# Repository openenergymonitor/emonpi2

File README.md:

# emonPi v2

The emonPi2 is an energy monitor that can monitor up to 6 AC circuits using CT sensors and the OpenEnergyMonitor emonVs voltage sensing unit. It consists of a measurement board that sits on top of a RaspberryPi. The measurement board features the Microchip AVR128DB348 microcontroller - responsible for sampling the current and voltage waveforms and calculating the power and energy values. The RaspberryPi provides full local data logging and visualisation capability. The emonPi2 can also be used as a basestation to receive data from other 433Mhz radio nodes.

**Features**

- 6 CT sensor inputs (333mV voltage output CT's)
- RJ45: 1-3 phase voltage input
- Pulse and temperature sensing input
- Micro: AVR128DB48
- MCP1501 Precision reference
- RFM69CW radio
- USB-C
- I2C 128x64 SSD1306 Display
- RTC I2C Breakout
- Optional on-board UART

### [Hardware schematic and board files](hardware)

### [Firmware](firmware)

### Community & Support

- [OpenEnergyMonitor Forums](https://community.openenergymonitor.org)

OpenEnergyMonitor Shop Support: support@openenergymonitor.zendesk.com

### License

- The hardware designs (schematics and CAD files) are licensed under a Creative Commons Attribution-ShareAlike 3.0 Unported License.
- The firmware is released under the GNU GPL V3 license The documentation is subject to GNU Free Documentation License
- The hardware designs follow the terms of the OSHW (Open-source hardware) Statement of Principles 1.0.

### Disclaimer

```
OUR PRODUCTS AND ASSEMBLY KITS MAY BE USED BY EXPERIENCED, SKILLED USERS, AT THEIR OWN RISK. TO THE FULLEST EXTENT PERMISSIBLE BY THE APPLICABLE LAW, WE HEREBY DISCLAIM ANY AND ALL RESPONSIBILITY, RISK, LIABILITY AND DAMAGES ARISING OUT OF DEATH OR PERSONAL INJURY RESULTING FROM ASSEMBLY OR OPERATION OF OUR PRODUCTS.

Your safety is your own responsibility, including proper use of equipment and safety gear, and determining whether you have adequate skill and experience. OpenEnergyMonitor and Megni registered partnership disclaims all responsibility for any resulting damage, injury, or expense. It is your responsibility to make sure that your activities comply with applicable laws, including copyright. Always check the webpage associated with each unit before you get started. There may be important updates or corrections. All use of the instructions, kits, projects and suggestions given both by megni.co.uk, openenergymonitor.org and shop.openenergymonitor.org are to be used at your own risk. The technology (hardware , firmware and software) are constantly changing, documentation (including build guide and instructions) may not be complete or correct.

If you feel uncomfortable with assembling or using any part of the system, return it to us for a full refund.
```

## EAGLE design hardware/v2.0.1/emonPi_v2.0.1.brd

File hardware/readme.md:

# emonPi2 - Hardware

## Change Log 

### V2.0.0

First release 

### V2.0.1

**manufactured in April 2023**

- DFM tweaks 
- Fix pad sizes 
- Change USB-C connector footprint and enable duel orientation data connections 

The emonPi2 hardware schematics and board files have been developed using Eagle (now Autodesk). A free version is available to download here: https://www.autodesk.co.uk/products/eagle/free-download.

Alternatively it is also possible to open these board designs using KiKad which is open source.

**Schematic:**

**Board design:**

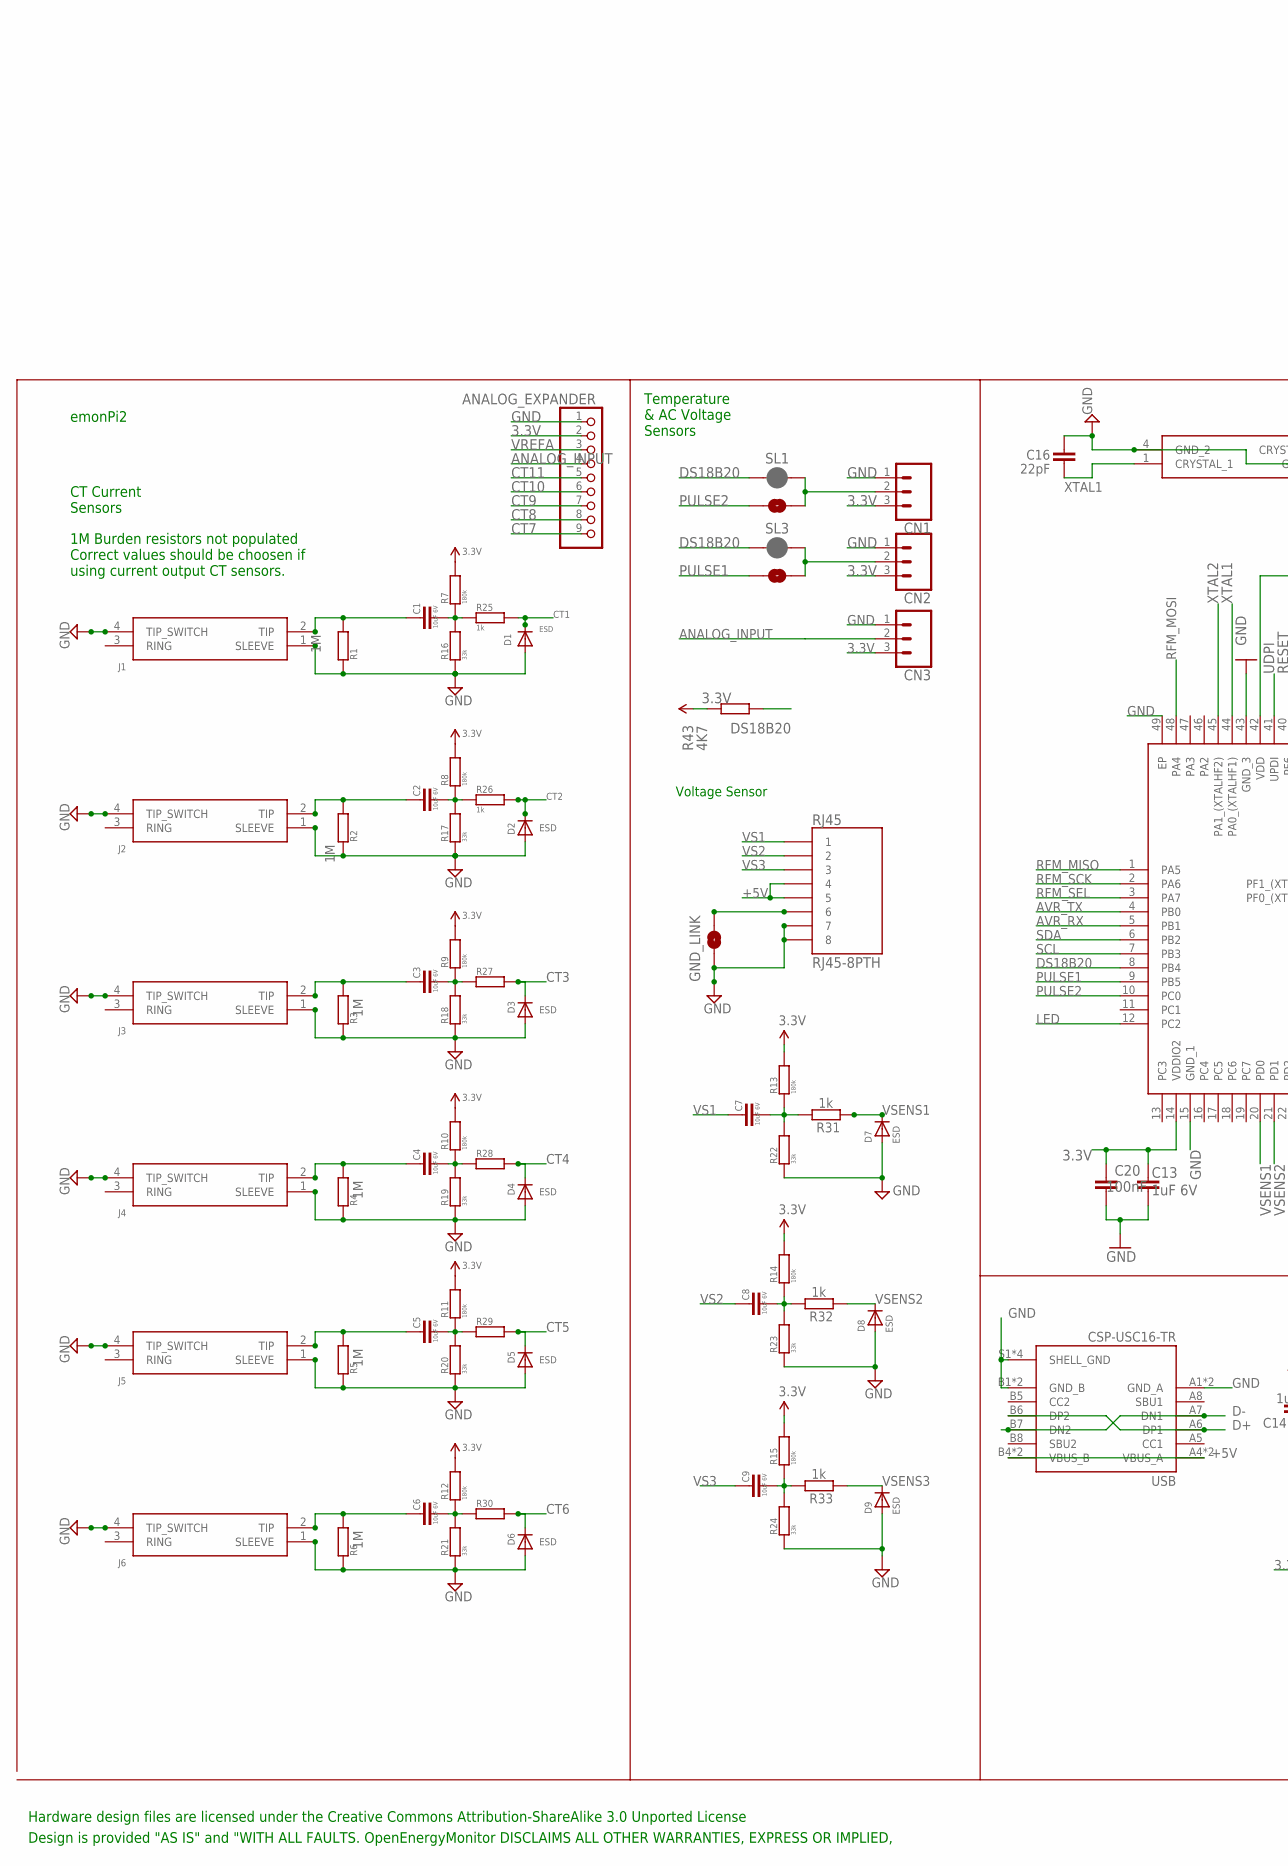
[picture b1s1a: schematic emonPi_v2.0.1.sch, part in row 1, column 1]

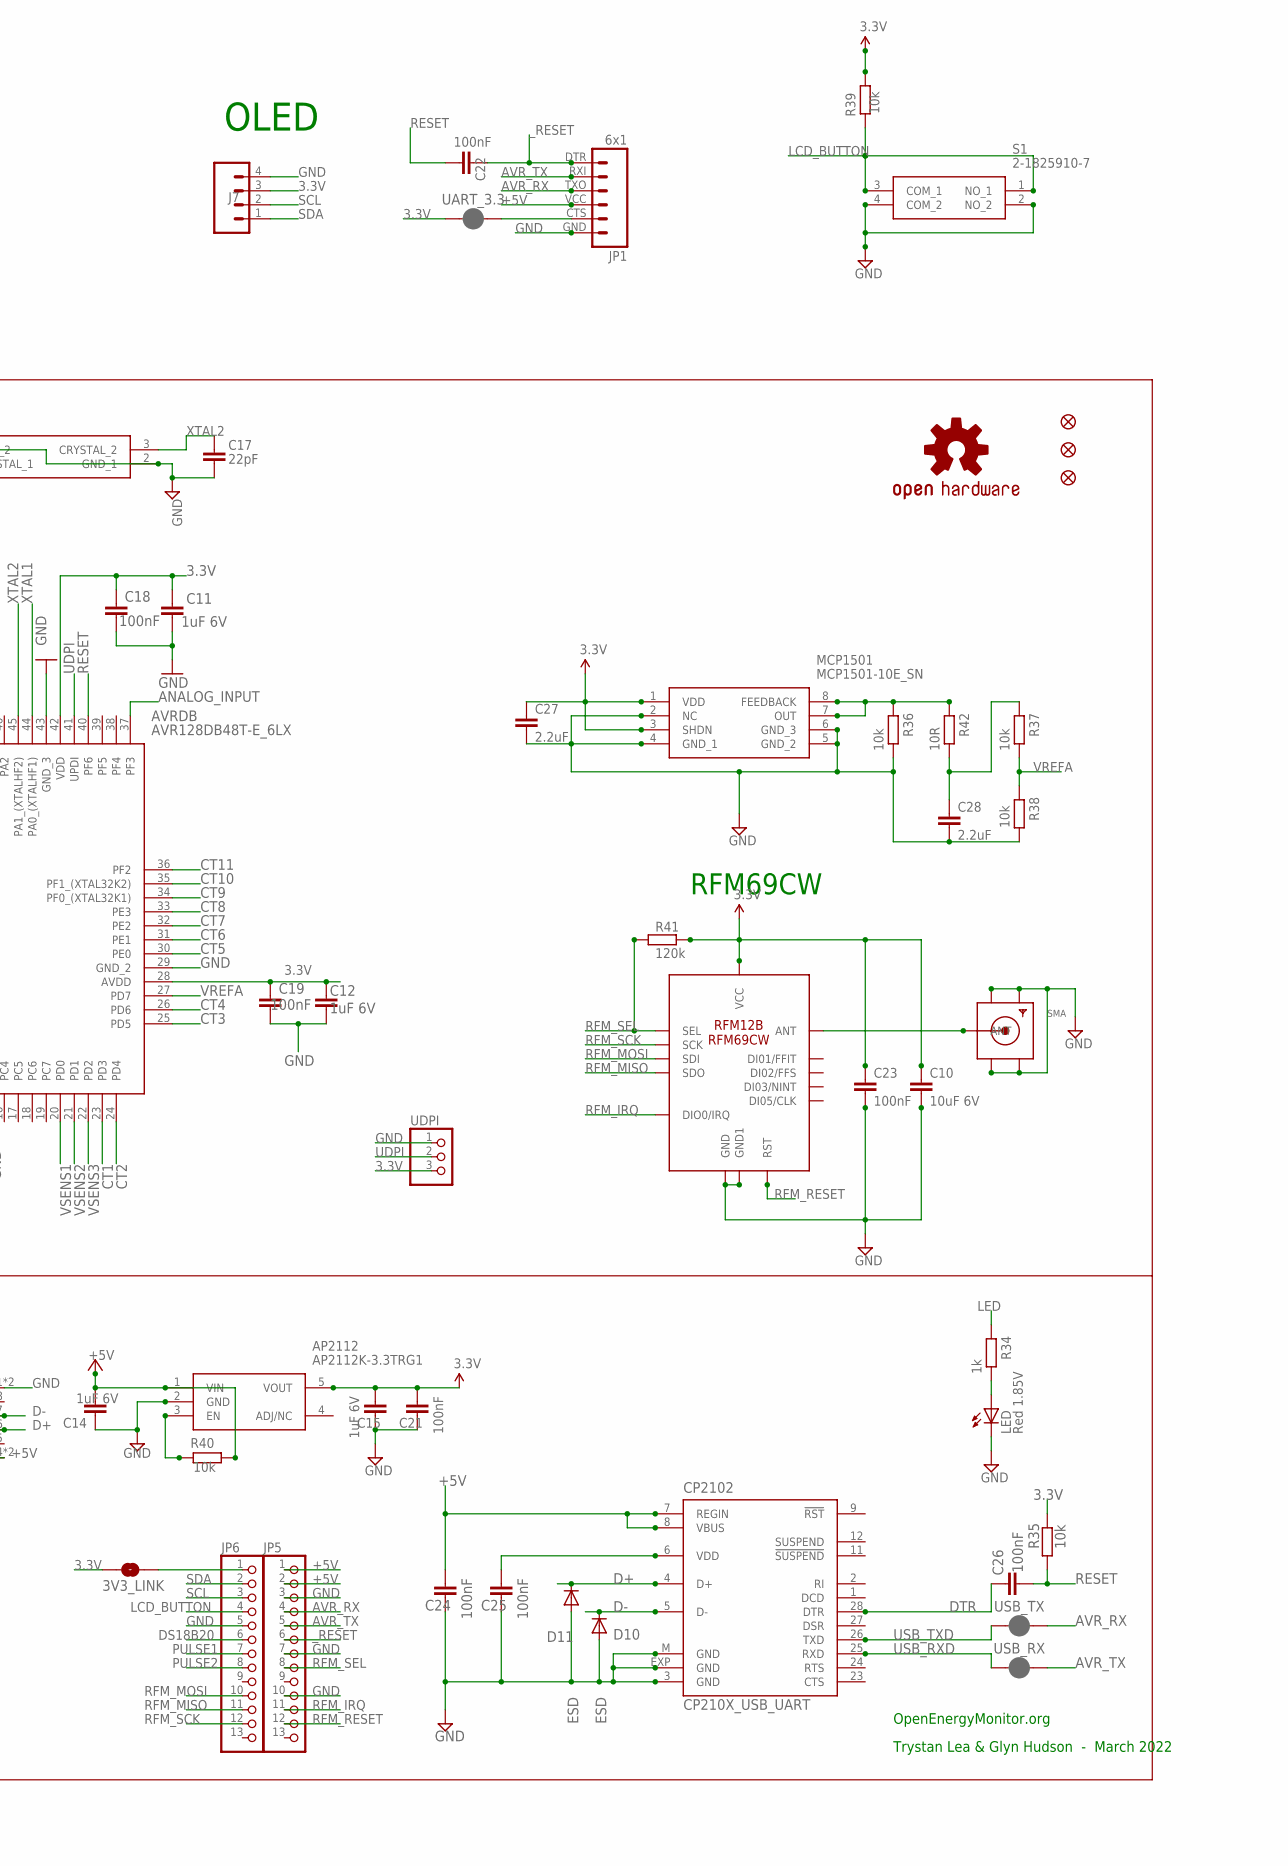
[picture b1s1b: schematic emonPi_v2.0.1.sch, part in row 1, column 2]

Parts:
3V3_LINK: SOLDERJUMPERNC; SJ_2S
ANALOG_EXPANDER: PINHD-1X9; 1X09-BIG
AP2112: AP2112K-3.3TRG1; SOT95P282X130-5N
AVRDB: AVR128DB48T-E_6LX; QFN40P600X600X90-49N
C1, C2, C3, C4, C5, C6, C7, C8, C9, C10: 10uF 6V; C0603
C11, C12, C13, C14, C15: 1uF 6V; C0603
C16, C17: 22pF; C0603
C18, C19, C20, C21, C22, C23, C24, C25, C26: 100nF; C0603
C27, C28: 2.2uF; C0603
CN1, CN2, CN3: CONN_03SCREW; SCREWTERMINAL-3.5MM-3
CP2102: CP210X_USB_UART; MLP28
D1, D2, D3, D4, D5, D6, D7, D8, D9, D10, D11: ESD; SOD-523
FD1, FD2, FD3: FIDUCIAL1X2; FIDUCIAL-1X2
GND_LINK: SOLDERJUMPERNC; SJ_2S
J1, J2, J3, J4, J5, J6: SJ-3524-SMT-TR
J7: CONN_04PTH; 1X04
JP1: 6x1; FTDI_BASIC
JP5, JP6: PINHD-1X13_BIG; 1X13-BIG
LED: Red 1.85V; CHIP-LED0805
LOGO1: OSHW-LOGOS-COPPER; OSHW-LOGO-S_COPPER
MCP1501: MCP1501-10E_SN; SOIC127P600X175-8N
R1, R2, R3, R4, R5, R6: 1M; R1206
R7, R8, R9, R10, R11, R12, R13, R14, R15: 180k; R0603
R16, R17, R18, R19, R20, R21, R22, R23, R24: 33k; R0603
R25, R26, R27, R28, R29, R30, R31, R32, R33, R34: 1k; R0603
R35, R36, R37, R38, R39, R40: 10k; R0603
R41: 120k; R0603
R42: 10R; R0603
R43: 4K7; R0603
RFM69: RFM12B/69CW
RJ45: RJ45-8PTH; RJ45-8
S1: 2-1825910-7; 218259107
SL1, SL3: JUMPER-SMT_2_NC_PASTE_NO-SILK; SMT-JUMPER_2_NC_PASTE_NO-SILK
SL2, SL4: SOLDERJUMPERNC; SJ_2S
SMA: SMACONNECTOR; SMA90_DIP
UART_3.3: JUMPER-SMT_2_NC_PASTE_NO-SILK; SMT-JUMPER_2_NC_PASTE_NO-SILK
UDPI: PINHD-1X3; 1X03
USB: CSP-USC16-TR; VALCON_CSP-USC16-TR
USB_RX: JUMPER-SMT_2_NC_PASTE_NO-SILK; SMT-JUMPER_2_NC_PASTE_NO-SILK
USB_TX: JUMPER-SMT_2_NC_PASTE_NO-SILK; SMT-JUMPER_2_NC_PASTE_NO-SILK
XTAL: MCSJK-7U-12.00-12-10-80-B-10; MCSJK7U1200121080B10

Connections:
3.3V: 3V3_LINK.1, ANALOG_EXPANDER.2, AP2112.5 (VOUT), AVRDB.14 (VDDIO2), AVRDB.28 (AVDD), AVRDB.42 (VDD), C10.1, C11.1, C12.1, C13.1, C15.2, C18.1, C19.1, C20.1, C21.2, C23.1, C27.1, CN1.3, CN2.3, CN3.3, J7.3, MCP1501.1 (VDD), MCP1501.3 (SHDN), R7.2, R8.2, R9.2, R10.2, R11.2, R12.2, R13.2, R14.2, R15.2, R35.2, R39.1, R41.2, R43.1, RFM69.VDD (VCC), UART_3.3.1, UDPI.3
+5V: AP2112.1 (VIN), C14.2, C24.2, CP2102.7 (REGIN), CP2102.8 (VBUS), JP1.VCC (4), JP5.1, JP5.2, R40.1, RJ45.4, RJ45.5, USB.A4 (VBUS_A), USB.A9 (VBUS_A), USB.B4 (VBUS_B), USB.B9 (VBUS_B)
ANALOG_INPUT: ANALOG_EXPANDER.4, AVRDB.37 (PF3), CN3.2
AVR_RX: AVRDB.5 (PB1), JP1.TXO (3), JP5.4, USB_TX.2
AVR_TX: AVRDB.4 (PB0), JP1.RXI (2), JP5.5, USB_RX.2
CT1: AVRDB.23 (PD3), D1.K (C), R25.2
CT2: AVRDB.24 (PD4), D2.K (C), R26.2
CT3: AVRDB.25 (PD5), D3.K (C), R27.1
CT4: AVRDB.26 (PD6), D4.K (C), R28.1
CT5: AVRDB.30 (PE0), D5.K (C), R29.1
CT6: AVRDB.31 (PE1), D6.K (C), R30.1
CT7: ANALOG_EXPANDER.9, AVRDB.32 (PE2)
CT8: ANALOG_EXPANDER.8, AVRDB.33 (PE3)
CT9: ANALOG_EXPANDER.7, AVRDB.34 (PF0_(XTAL32K1))
CT10: ANALOG_EXPANDER.6, AVRDB.35 (PF1_(XTAL32K2))
CT11: ANALOG_EXPANDER.5, AVRDB.36 (PF2)
D+: CP2102.4 (D+), D11.K (C), USB.A6 (DP1), USB.B6 (DP2)
D-: CP2102.5 (D-), D10.K (C), USB.A7 (DN1), USB.B7 (DN2)
DIG1: RFM69.ANT, SMA.ANTENNA (ANT)
DS18B20: AVRDB.8 (PB4), JP6.6, R43.2, SL1.1, SL3.1
DTR: C26.1, CP2102.28 (DTR)
GND: ANALOG_EXPANDER.1, AP2112.2 (GND), AVRDB.15 (GND_1), AVRDB.29 (GND_2), AVRDB.43 (GND_3), AVRDB.49 (EP), C10.2, C11.2, C12.2, C13.2, C14.1, C15.1, C16.1, C17.2, C18.2, C19.2, C20.2, C21.1, C23.2, C24.1, C25.1, C27.2, C28.2, CN1.1, CN2.1, CN3.1, CP2102.3 (GND), CP2102.EXP (GND), CP2102.M (GND), D1.A, D2.A, D3.A, D4.A, D5.A, D6.A, D7.A, D8.A, D9.A, D10.A, D11.A, GND_LINK.1, J1.1 (SLEEVE), J1.4 (TIP_SWITCH), J2.1 (SLEEVE), J2.4 (TIP_SWITCH), J3.1 (SLEEVE), J3.4 (TIP_SWITCH), J4.1 (SLEEVE), J4.4 (TIP_SWITCH), J5.1 (SLEEVE), J5.4 (TIP_SWITCH), J6.1 (SLEEVE), J6.4 (TIP_SWITCH), J7.4, JP1.GND (6), JP5.3, JP5.7, JP5.10, JP6.5, LED.C, MCP1501.2 (NC), MCP1501.4 (GND_1), MCP1501.5 (GND_2), MCP1501.6 (GND_3), R1.1, R2.1, R3.1, R4.1, R5.1, R6.1, R16.2, R17.2, R18.2, R19.2, R20.2, R21.2, R22.2, R23.1, R24.1, R36.1, R38.1, RFM69.GND, RFM69.GND1, RJ45.7, RJ45.8, S1.2 (NO_2), S1.4 (COM_2), SMA.GND1, SMA.GND2, SMA.GND3, SMA.GND4, UDPI.1, USB.A1 (GND_A), USB.A12 (GND_A), USB.B1 (GND_B), USB.B12 (GND_B), USB.S1 (SHELL_GND), USB.S2 (SHELL_GND), USB.S3 (SHELL_GND), USB.S4 (SHELL_GND), XTAL.2 (GND_1), XTAL.4 (GND_2)
LCD_BUTTON: JP6.4, R39.2, S1.1 (NO_1), S1.3 (COM_1)
LED: AVRDB.12 (PC2), R34.2
unnamed: C1.1, J1.2 (TIP), R1.2
unnamed: C7.2, R13.1, R22.1, R31.2
unnamed: C3.1, J3.2 (TIP), R3.2
unnamed: C8.2, R14.1, R23.2, R32.2
unnamed: C4.1, J4.2 (TIP), R4.2
unnamed: C9.2, R15.1, R24.2, R33.2
unnamed: C2.1, J2.2 (TIP), R2.2
unnamed: C5.1, J5.2 (TIP), R5.2
unnamed: C5.2, R11.1, R20.1, R29.2
unnamed: C2.2, R8.1, R17.1, R26.1
unnamed: C4.2, R10.1, R19.1, R28.2
unnamed: C1.2, R7.1, R16.1, R25.1
unnamed: C6.1, J6.2 (TIP), R6.2
unnamed: C6.2, R12.1, R21.1, R30.2
unnamed: C3.2, R9.1, R18.1, R27.2
unnamed: CN1.2, SL1.2, SL2.2
unnamed: CN2.2, SL3.2, SL4.2
unnamed: GND_LINK.2, RJ45.6
unnamed: AP2112.3 (EN), R40.2
unnamed: C28.1, R37.2, R42.1
unnamed: MCP1501.7 (OUT), MCP1501.8 (FEEDBACK), R36.2, R42.2
unnamed: 3V3_LINK.2, JP6.1
unnamed: C25.2, CP2102.6 (VDD)
unnamed: JP1.CTS (5), UART_3.3.2
unnamed: LED.A, R34.1
PULSE1: AVRDB.9 (PB5), JP6.7, SL4.1
PULSE2: AVRDB.10 (PC0), JP6.8, SL2.1
RESET: AVRDB.40 (PF6), C22.2, C26.2, R35.1
RFM_IRQ: JP5.11, RFM69.IRQ (DIO0/IRQ)
RFM_MISO: AVRDB.1 (PA5), JP6.11, RFM69.SDO
RFM_MOSI: AVRDB.48 (PA4), JP6.10, RFM69.SDI
RFM_RESET: JP5.12, RFM69.RST
RFM_SCK: AVRDB.2 (PA6), JP6.12, RFM69.SCK
RFM_SEL: AVRDB.3 (PA7), JP5.8, R41.1, RFM69.SEL
SCL: AVRDB.7 (PB3), J7.2, JP6.3
SDA: AVRDB.6 (PB2), J7.1, JP6.2
UDPI: AVRDB.41 (UPDI), UDPI.2
USB_RXD: CP2102.25 (RXD), USB_RX.1
USB_TXD: CP2102.26 (TXD), USB_TX.1
VREFA: ANALOG_EXPANDER.3, AVRDB.27 (PD7), R37.1, R38.2
VS1: C7.1, RJ45.1
VS2: C8.1, RJ45.2
VS3: C9.1, RJ45.3
VSENS1: AVRDB.20 (PD0), D7.K (C), R31.1
VSENS2: AVRDB.21 (PD1), D8.K (C), R32.1
VSENS3: AVRDB.22 (PD2), D9.K (C), R33.1
XTAL1: AVRDB.44 (PA0_(XTALHF1)), C16.2, XTAL.1 (CRYSTAL_1)
XTAL2: AVRDB.45 (PA1_(XTALHF2)), C17.1, XTAL.3 (CRYSTAL_2)
_RESET: C22.1, JP1.DTR (1), JP5.6

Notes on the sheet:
Voltage Sensor
RFM69CW
OLED
emonPi2
Temperature & AC Voltage Sensors
Design is provided "AS IS" and "WITH ALL FAULTS. OpenEnergyMonitor DISCLAIMS ALL OTHER WARRANTIES, EXPRESS OR IMPLIED,
Hardware design files are licensed under the Creative Commons Attribution-ShareAlike 3.0 Unported License
OpenEnergyMonitor.org
Trystan Lea & Glyn Hudson - March 2022
1M Burden resistors not populated Correct values should be choosen if using current output CT sensors.
CT Current Sensors

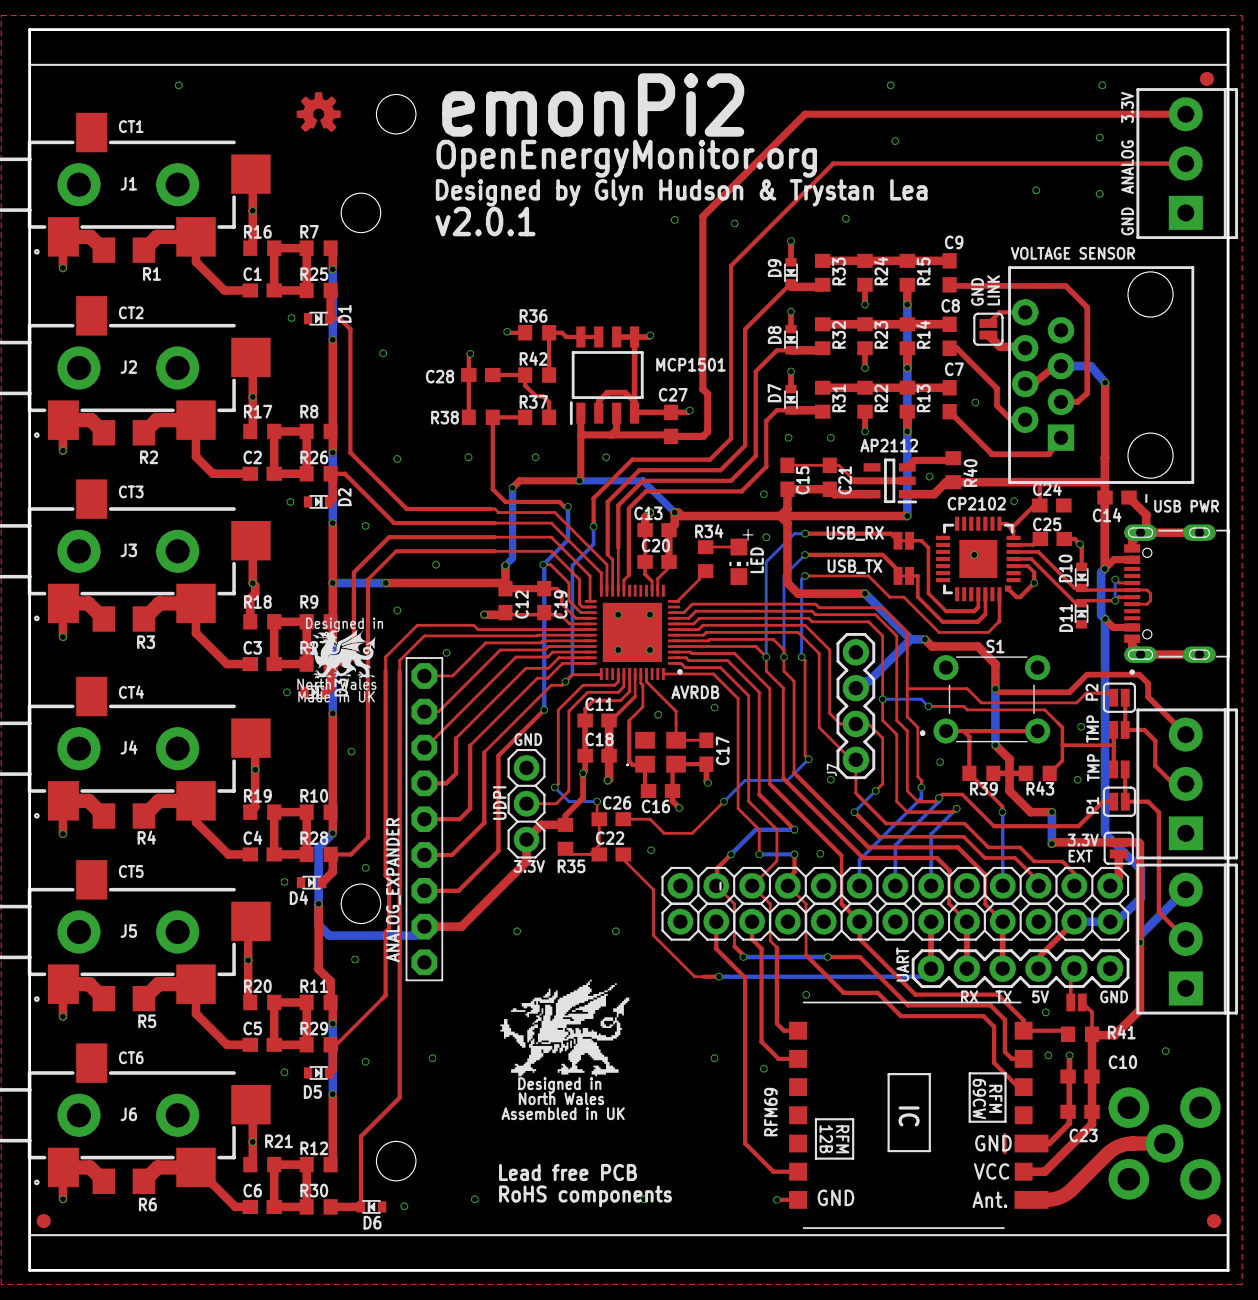
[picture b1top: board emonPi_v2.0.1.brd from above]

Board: 2 copper layers, 85.0 x 88.0 mm, 121 parts (0 on the bottom side), 73 nets.

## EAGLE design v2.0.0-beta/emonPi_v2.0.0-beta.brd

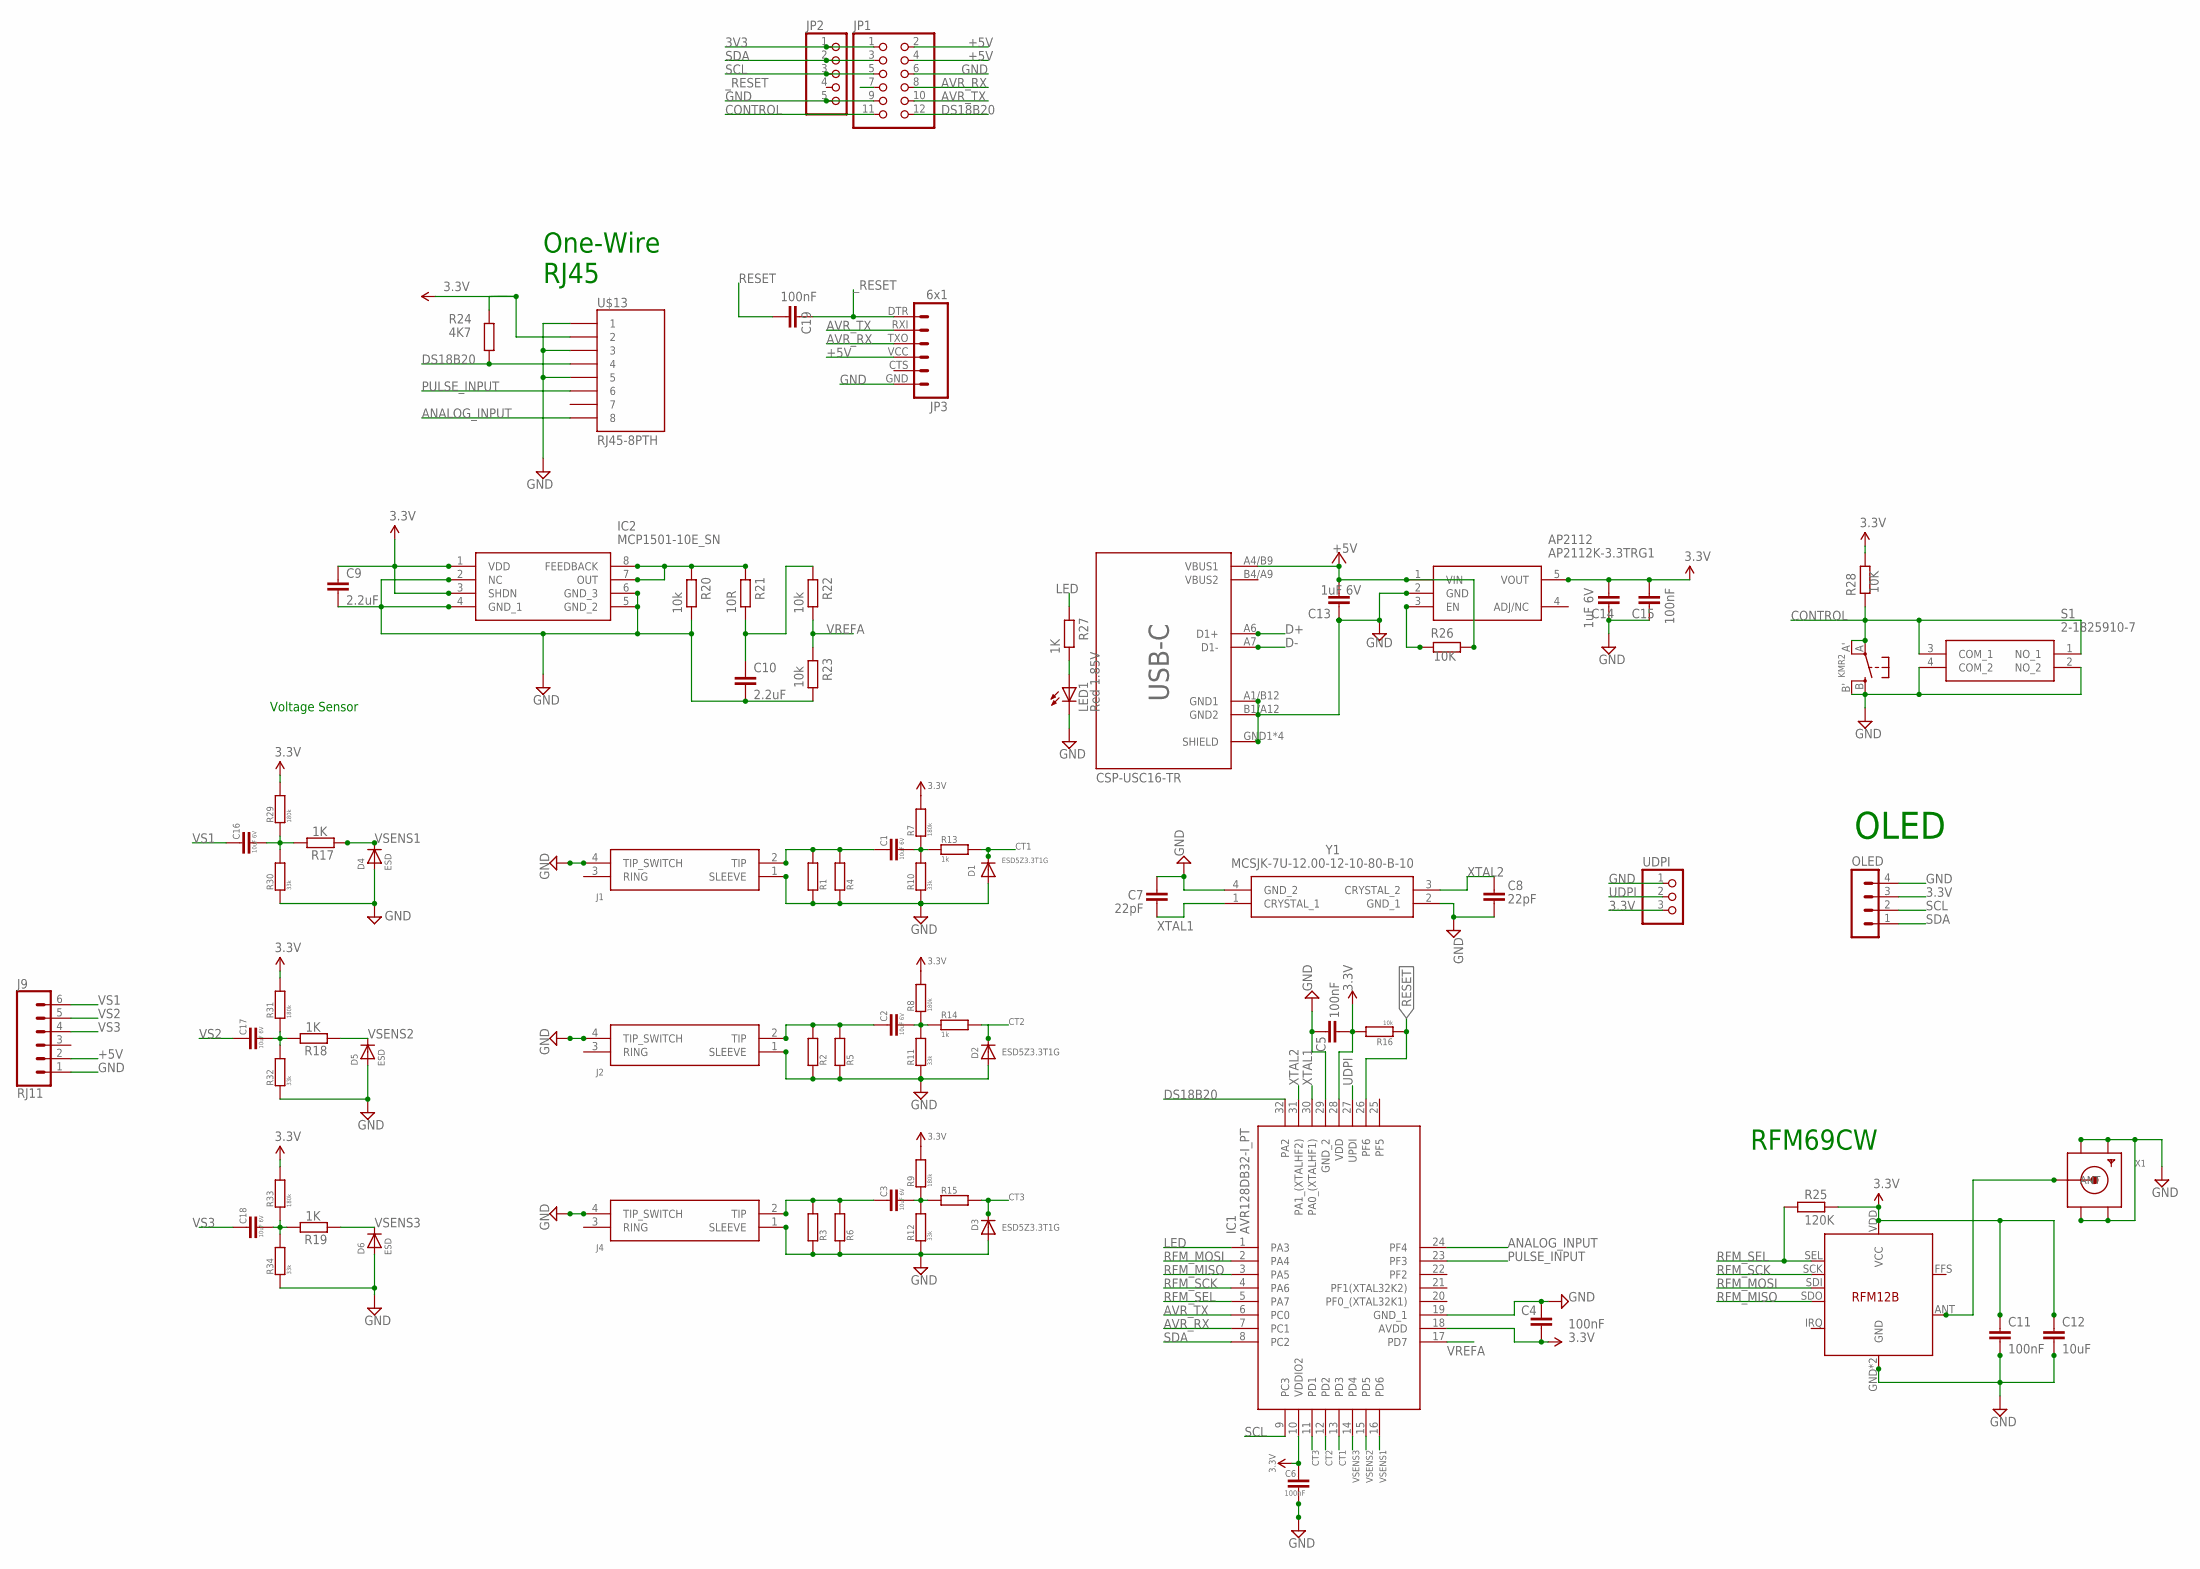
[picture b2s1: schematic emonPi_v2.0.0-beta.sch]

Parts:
AP2112: AP2112K-3.3TRG1; SOT95P282X130-5N
C1, C2, C3, C16, C17, C18: 10uF 6V; C0603
C4, C5, C6, C11, C15, C19: 100nF; C0603
C7, C8: 22pF; C0603
C9, C10: 2.2uF; C0603
C12: 10uF; C0603
C13, C14: 1uF 6V; C0603
CTRL: KMR2; BTN_KMR2_4.6X2.8
D1, D2, D3: ESD5Z3.3T1G; SOD-523
D4, D5, D6: ESD; SOD-523
IC1: AVR128DB32-I_PT; QFP80P900X900X120-32N
IC2: MCP1501-10E_SN; SOIC127P600X175-8N
J1, J2, J4: SJ-3524-SMT-TR
J9: RJ11; RJ11-6
JP1: PINHD-2X6; 2X06
JP2: PINHD-1X5; 1X05
JP3: 6x1; FTDI_BASIC
LED1: Red 1.85V; CHIP-LED0805
OLED: MA04-1-OLEDOLED; MA04-1-OLED
R1, R2, R3: R-EU_R1206; R1206
R4, R5, R6: R-EU_0204/7; 0204/7
R7, R8, R9, R29, R31, R33: 180k; R0603
R10, R11, R12, R30, R32, R34: 33k; R0603
R13, R14, R15: 1k; R0603
R16, R20, R22, R23: 10k; R0603
R17, R18, R19, R27: 1K; R0603
R21: 10R; R0603
R24: 4K7; R0603
R25: 120K; R0603
R26, R28: 10K; R0603
S1: 2-1825910-7; 218259107
U$13: RJ45-8PTH; RJ45-8
U$14: RFM12B
UDPI: PINHD-1X3; 1X03
USB-C: CSP-USC16-TR; USB-C
X1: SMACONNECTOR; SMA90_DIP
Y1: MCSJK-7U-12.00-12-10-80-B-10; MCSJK7U1200121080B10

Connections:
3.3V: AP2112.5 (VOUT), C4.1, C5.2, C6.1, C9.1, C11.1, C12.1, C14.2, C15.2, IC1.10 (VDDIO2), IC1.18 (AVDD), IC1.28 (VDD), IC2.1 (VDD), IC2.3 (SHDN), OLED.3, R7.2, R8.2, R9.2, R16.2, R24.1, R25.2, R28.1, R29.2, R31.2, R33.2, U$13.2, U$14.VDD (VCC), UDPI.3
3V3: JP1.1, JP2.1
+5V: AP2112.1 (VIN), C13.2, J9.2, JP1.2, JP1.4, JP3.VCC (4), R26.1, USB-C.A4/B9 (VBUS1)
ANALOG_INPUT: IC1.24 (PF4), U$13.8
AVR_RX: IC1.7 (PC1), JP1.8, JP3.TXO (3)
AVR_TX: IC1.6 (PC0), JP1.10, JP3.RXI (2)
CONTROL: CTRL.A, CTRL.A' (P1), JP1.11, R28.2, S1.1 (NO_1), S1.3 (COM_1)
CT1: D1.K (C), IC1.13 (PD3), R13.2
CT2: D2.K (C), IC1.12 (PD2), R14.2
CT3: D3.K (C), IC1.11 (PD1), R15.1
D+: USB-C.A6 (D1+)
D-: USB-C.A7 (D1-)
DIG1: U$14.ANT, X1.ANTENNA (ANT)
DS18B20: IC1.32 (PA2), JP1.12, R24.2, U$13.4
GND: AP2112.2 (GND), C4.2, C5.1, C6.2, C7.1, C8.2, C9.2, C10.2, C11.2, C12.2, C13.1, C14.1, C15.1, CTRL.B (S), CTRL.B' (S1), D1.A, D2.A, D3.A, D4.A, D5.A, D6.A, IC1.19 (GND_1), IC1.29 (GND_2), IC2.2 (NC), IC2.4 (GND_1), IC2.5 (GND_2), IC2.6 (GND_3), J1.1 (SLEEVE), J1.4 (TIP_SWITCH), J2.1 (SLEEVE), J2.4 (TIP_SWITCH), J4.1 (SLEEVE), J4.4 (TIP_SWITCH), J9.1, JP1.6, JP1.9, JP2.5, JP3.GND (6), LED1.C, OLED.4, R1.1, R2.1, R3.1, R4.1, R5.1, R6.1, R10.2, R11.2, R12.2, R20.1, R23.1, R30.2, R32.1, R34.1, S1.2 (NO_2), S1.4 (COM_2), U$13.1, U$13.3, U$13.5, U$14.GND, U$14.P$12 (GND), UDPI.1, USB-C.A1/B12 (GND1), USB-C.B1/A12 (GND2), USB-C.GND1 (SHIELD), USB-C.GND2 (SHIELD), USB-C.GND3 (SHIELD), USB-C.GND4 (SHIELD), X1.GND1, X1.GND2, X1.GND3, X1.GND4, Y1.2 (GND_1), Y1.4 (GND_2)
LED: IC1.1 (PA3), R27.2
unnamed: C1.1, J1.2 (TIP), R1.2, R4.2
unnamed: C16.2, R17.2, R29.1, R30.1
unnamed: C3.1, J4.2 (TIP), R3.2, R6.2
unnamed: C17.2, R18.2, R31.1, R32.2
unnamed: C18.2, R19.2, R33.1, R34.2
unnamed: C2.1, J2.2 (TIP), R2.2, R5.2
unnamed: C10.1, R21.1, R22.2
unnamed: AP2112.3 (EN), R26.2
unnamed: C2.2, R8.1, R11.1, R14.1
unnamed: C1.2, R7.1, R10.1, R13.1
unnamed: C3.2, R9.1, R12.1, R15.2
unnamed: IC2.7 (OUT), IC2.8 (FEEDBACK), R20.2, R21.2
unnamed: LED1.A, R27.1
PULSE_INPUT: IC1.23 (PF3), U$13.6
RESET: C19.2, IC1.26 (PF6), R16.1
RFM_MISO: IC1.3 (PA5), U$14.SDO
RFM_MOSI: IC1.2 (PA4), U$14.SDI
RFM_SCK: IC1.4 (PA6), U$14.SCK
RFM_SEL: IC1.5 (PA7), R25.1, U$14.SEL
SCL: IC1.9 (PC3), JP1.5, JP2.3, OLED.2
SDA: IC1.8 (PC2), JP1.3, JP2.2, OLED.1
UDPI: IC1.27 (UPDI), UDPI.2
VREFA: IC1.17 (PD7), R22.1, R23.2
VS1: C16.1, J9.6
VS2: C17.1, J9.5
VS3: C18.1, J9.4
VSENS1: D4.K (C), IC1.16 (PD6), R17.1
VSENS2: D5.K (C), IC1.15 (PD5), R18.1
VSENS3: D6.K (C), IC1.14 (PD4), R19.1
XTAL1: C7.2, IC1.30 (PA0_(XTALHF1)), Y1.1 (CRYSTAL_1)
XTAL2: C8.1, IC1.31 (PA1_(XTALHF2)), Y1.3 (CRYSTAL_2)
_RESET: C19.1, JP1.7, JP3.DTR (1)

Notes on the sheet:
Voltage Sensor
One-Wire RJ45
RFM69CW
OLED

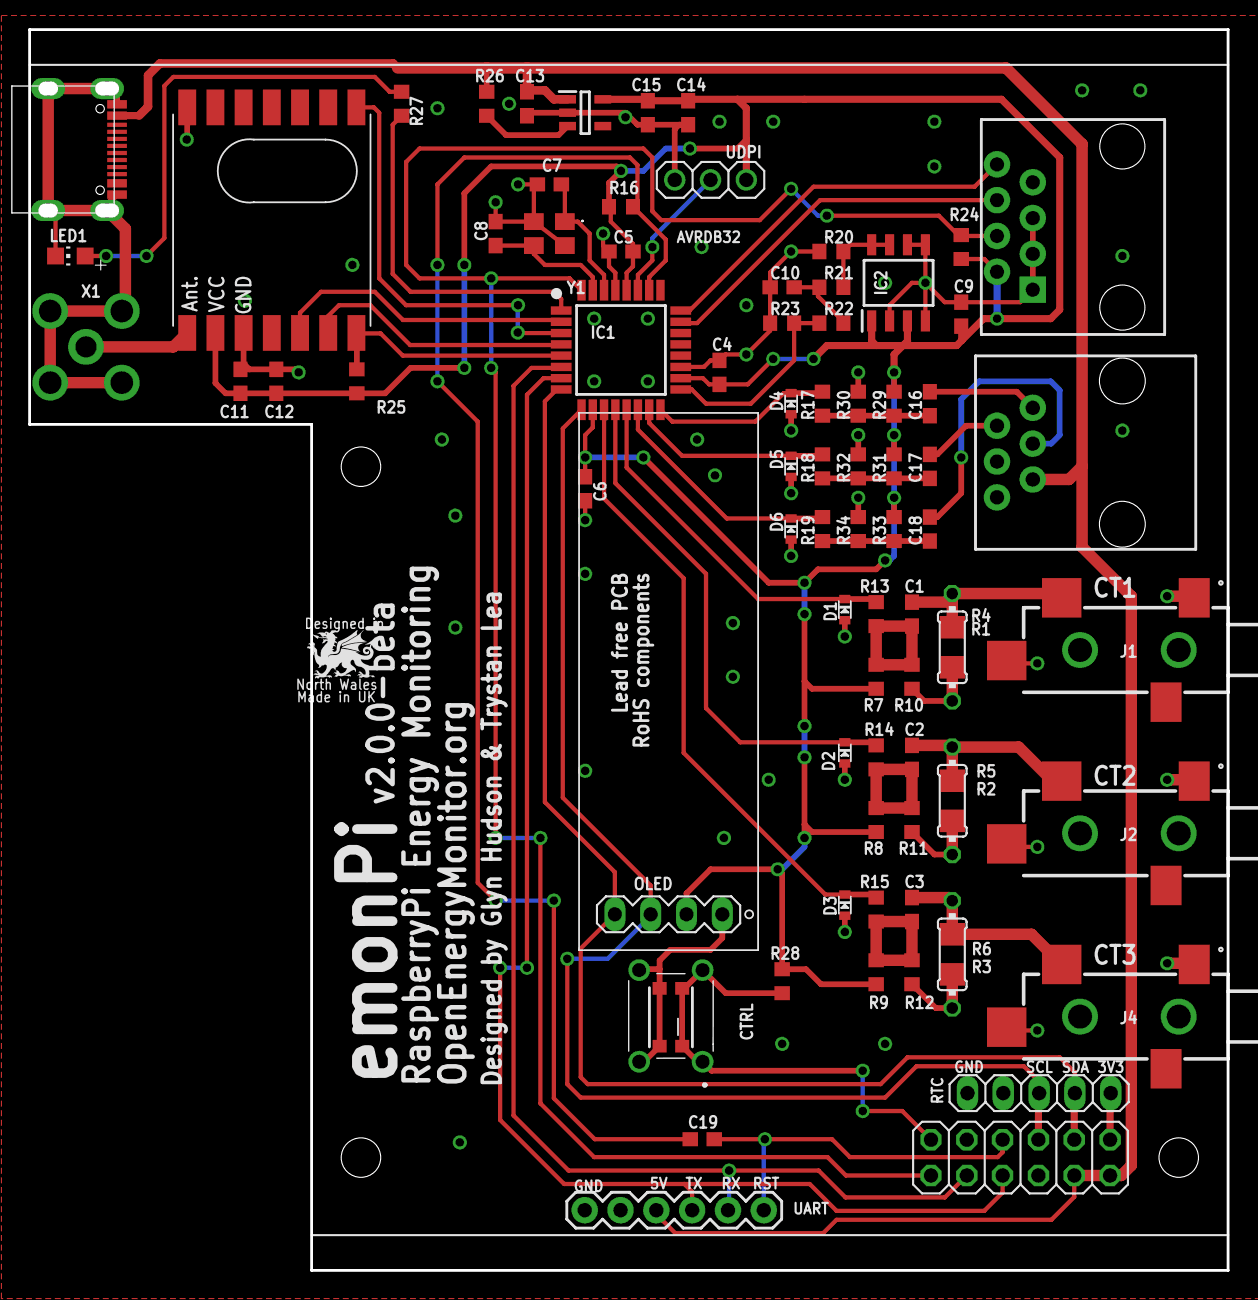
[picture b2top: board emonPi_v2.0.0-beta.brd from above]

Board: 2 copper layers, 85.0 x 88.0 mm, 79 parts (0 on the bottom side), 46 nets.

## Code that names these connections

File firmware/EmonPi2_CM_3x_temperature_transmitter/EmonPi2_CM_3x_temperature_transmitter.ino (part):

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                                                           // For safety, thus MUST default to false. (Required due to faulty ESP8266 software.)

//----------------------------emonTx V4 hard-wired connections-----------------------------------
const byte LEDpin      = PIN_PC2;  // emonTx V4 LED

//---------------------------------CT availability status----------------------------------------
byte CT_count = 0;
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    
    // Frequency is currently hardcoded to 433Mhz in library
    #if RadioFormat == RFM69_LOW_POWER_LABS
    rf.setPins(PIN_PA7,PIN_PA4,PIN_PA5,PIN_PA6);
    #endif
    rf.initialize(RF69_433MHZ, EEProm.nodeID, EEProm.networkGroup); 
    rf.encrypt("89txbe4p8aik5kt3"); // ignored if jeelib classic
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  EmonLibCM_setAssumedVrms(EEProm.assumedVrms);

  EmonLibCM_setPulseEnable(EEProm.pulse_enable);                       // Enable pulse counting
  EmonLibCM_setPulsePin(PIN_PB5);                                      // Pulse 1 (can also be PC0: Pulse 2)
  EmonLibCM_setPulseMinPeriod(EEProm.pulse_period);

  EmonLibCM_setTemperatureDataPin(PIN_PB4);                            // OneWire data pin (emonTx V4)
  EmonLibCM_setTemperaturePowerPin(PIN_PC1);                           // Temperature sensor Power Pin - 19 for emonTx V4  (-1 = Not used. No sensors, or sensor are permanently powered.)
  EmonLibCM_setTemperatureResolution(11);                              // Resolution in bits, allowed values 9 - 12. 11-bit resolution, reads to 0.125 degC
  EmonLibCM_setTemperatureAddresses(EEProm.allAddresses);              // Name of array of temperature sensors
  EmonLibCM_setTemperatureArray(allTemps);                             // Name of array to receive temperature measurements
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        Serial.print(F(",I6:")); Serial.print(EmonLibCM_getIrms(EmonLibCM_getLogicalChannel(6)),3);
        
        Serial.print(F(",pf1:")); Serial.print(EmonLibCM_getPF(EmonLibCM_getLogicalChannel(1)),4);
        Serial.print(F(",pf2:")); Serial.print(EmonLibCM_getPF(EmonLibCM_getLogicalChannel(2)),4);
        Serial.print(F(",pf3:")); Serial.print(EmonLibCM_getPF(EmonLibCM_getLogicalChannel(3)),4);
        Serial.print(F(",pf4:")); Serial.print(EmonLibCM_getPF(EmonLibCM_getLogicalChannel(4)),4);
        Serial.print(F(",pf5:")); Serial.print(EmonLibCM_getPF(EmonLibCM_getLogicalChannel(5)),4);
        Serial.print(F(",pf6:")); Serial.println(EmonLibCM_getPF(EmonLibCM_getLogicalChannel(6)),4);
        delay(80);
      }
    }
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
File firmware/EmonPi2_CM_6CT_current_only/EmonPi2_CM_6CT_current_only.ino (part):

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                                                           // For safety, thus MUST default to false. (Required due to faulty ESP8266 software.)

//----------------------------emonTx V4 hard-wired connections-----------------------------------
const byte LEDpin      = PIN_PC2;  // emonTx V4 LED

//----------------------------------------Setup--------------------------------------------------
void setup() 
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  oled.print("starting...");
  Wire1.end();

  pinMode(PIN_PB2,INPUT);
  pinMode(PIN_PB3,INPUT);

  //wdt_enable(WDTO_8S);
  
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    
    // Frequency is currently hardcoded to 433Mhz in library
    #if RadioFormat == RFM69_LOW_POWER_LABS
    rf.setPins(PIN_PA7,PIN_PA4,PIN_PA5,PIN_PA6);
    #endif
    rf.initialize(RF69_433MHZ, EEProm.nodeID, EEProm.networkGroup); 
    rf.encrypt("89txbe4p8aik5kt3"); // ignored if jeelib classic
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
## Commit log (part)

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2022-06-17 emonPi2 schematic and board file
2022-06-17 images
2022-06-26 rfm69pi designs
2022-07-06 firmware
2022-07-06 new firmware
2022-07-06 RFM6n rx tx firmware example
2022-07-08 readme
2022-07-08 smaller image
2022-07-08 firmware readme in progress
2022-07-08 update image
2022-07-08 updated image
2022-07-08 firmware documentation
2022-07-08 compilation settings
2022-07-12 emonpi2 fascia
2022-07-12 updated board file
2022-07-12 fix push switch
2022-07-13 first attempt at compiling using pio
2022-07-14 add libs
2023-04-04 emonPi v2 redesigned to use AVR128DB48++
2023-04-05 export
2023-04-16 Blink example and EmonPi2 firmware
2023-04-16 examples
2023-04-16 fix print currents and PF
2023-04-16 fascias
2023-04-17 updated fascia
2023-04-17 fascias and CT expansion board
2023-04-17 update EmonPi2_Tx to use main RFM6_LPL branch
2023-04-17 fascia text
2023-04-19 dxcore onewire
2023-04-19 update platformio to use emonlibcm onewire_isr_fix
2023-05-03 add fascia export and CAM file
2023-05-03 changelog
2023-05-04 add paneled garbers
2023-05-04 component label positions
2023-05-19 factory test
2023-05-19 check radio
2023-05-19 print radio status to serial
2023-05-19 platformio
2023-07-07 update front page image
2023-07-07 emonPi2 image
2023-07-07 overview docs
2023-07-07 update overview
2023-07-19 latest fascia design
2023-07-21 fix lib versions
2023-07-21 rename emontx4 to emonpi2
2023-07-26 fascia designs
2023-08-02 updated emonpi2 tx firmware
2023-08-02 EmonPi2 Firmware
2023-08-02 compiled hex
2023-09-06 dxf export of top plate
2023-09-07 longer sd card slot to support pi zero
2023-09-07 archive rev1 fascias
2023-09-07 update fascias
2023-10-06 add dimentions
2023-10-09 vector files fascias
2023-11-07 fascia amendments 7th Nov
2023-11-07 revised back
2023-11-07 updated dxf
2023-11-07 updated dimension
2023-11-17 LCD support
2023-11-17 update version
2023-11-17 new hex file
2023-11-17 move to compiled
2023-11-30 updated firmware
2023-11-30 partial emonpi2 documentation
2023-11-30 update firmware list
2023-11-30 update firmware descriptions
2023-11-30 upload and compile
2023-11-30 update other sensors
2023-12-01 update documentation
2023-12-01 update docs
2023-12-01 analog input example
2023-12-15 example of pulse on analog
2023-12-21 voltage sensor pinout
2023-12-21 pinout
2024-01-02 emonVs test jig
2024-01-02 current only example
2024-01-08 add emonpi starting message to the LCD
2024-01-08 updated hex
2024-01-16 update emonPi2 firmware
2024-01-16 update pulse counting section
2024-01-16 update emonupload list
2024-01-31 Fix broken link
    Fix broken link
2024-02-09 updated setup documentation
2024-02-10 updated install guide
2024-03-14 10ms pulse firmware
2024-03-14 updated pulse on analog trying 5ms
2024-03-14 new hex
2024-03-15 2ms pulse count
2024-04-26 remove comments
2024-04-26 3phase pulse on analog
2024-04-26 update print
2024-05-14 firmware has now moved to avrdb_firmware
2024-05-14 change alignment
2024-05-15 update emonPi2 docs for latest firmware
2024-05-26 current only
2024-05-26 3-phase 4-wire and n,american systems
2025-03-03 doc: Link to git repo which contains emonupload.py
2025-03-03 doc: corrected the link at the end of the Quick Start instructions
2025-03-03 doc: corrected the "Edit on GitHub" link
2025-03-03 doc: added notes for the emonVs power supply/voltage sensor
2025-04-30 add install video

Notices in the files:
firmware/EmonPi2_CM_3x_temperature_transmitter/EmonPi2_CM_3x_temperature_transmitter.ino:
Licence: GNU GPL V3
parts and their libraries:
SparkFun-Connectors: Licensing: CC v3.0 Share-Alike You are welcome to use this library for commercial purposes.
microbuilder: This work is placed in the public domain, and may be freely used for commercial and non-commercial work with the following conditions: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
